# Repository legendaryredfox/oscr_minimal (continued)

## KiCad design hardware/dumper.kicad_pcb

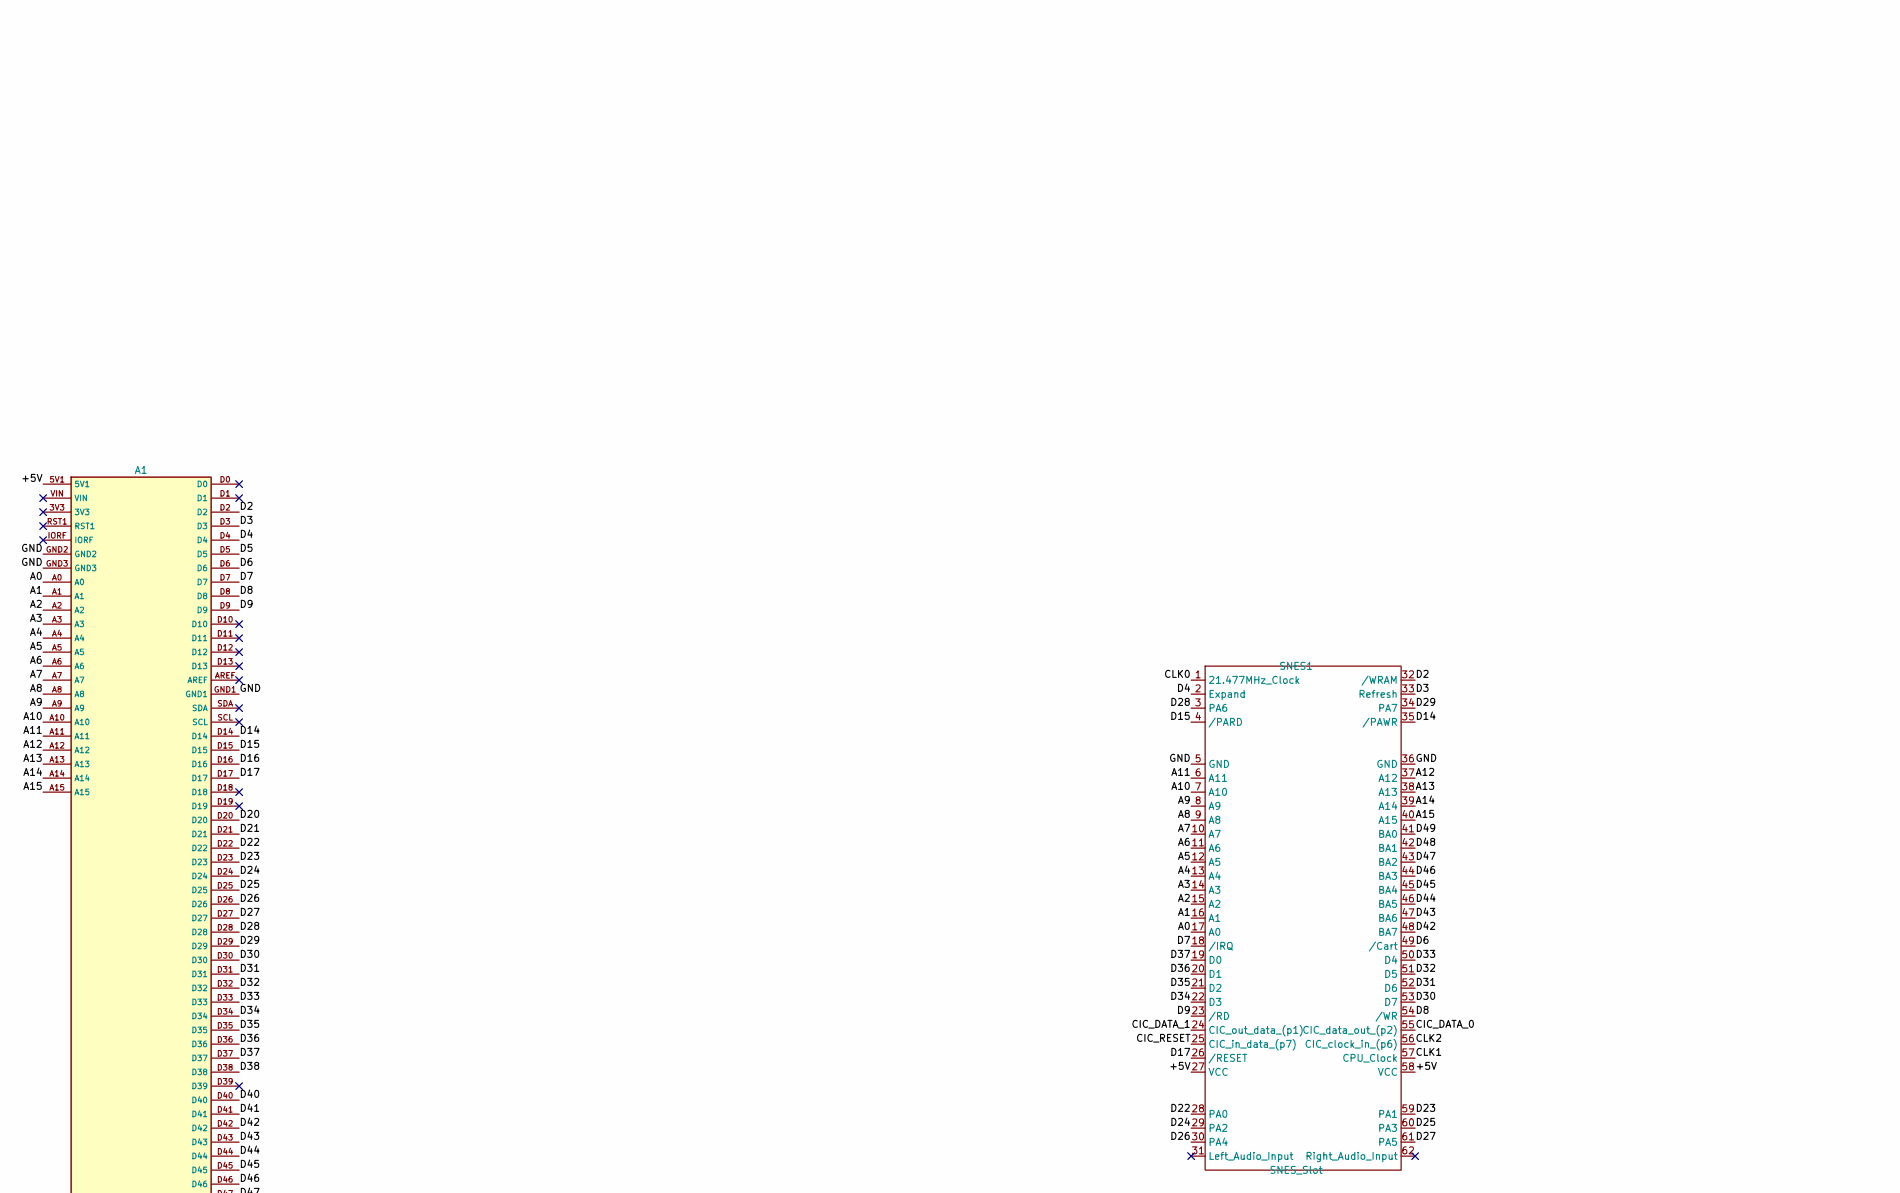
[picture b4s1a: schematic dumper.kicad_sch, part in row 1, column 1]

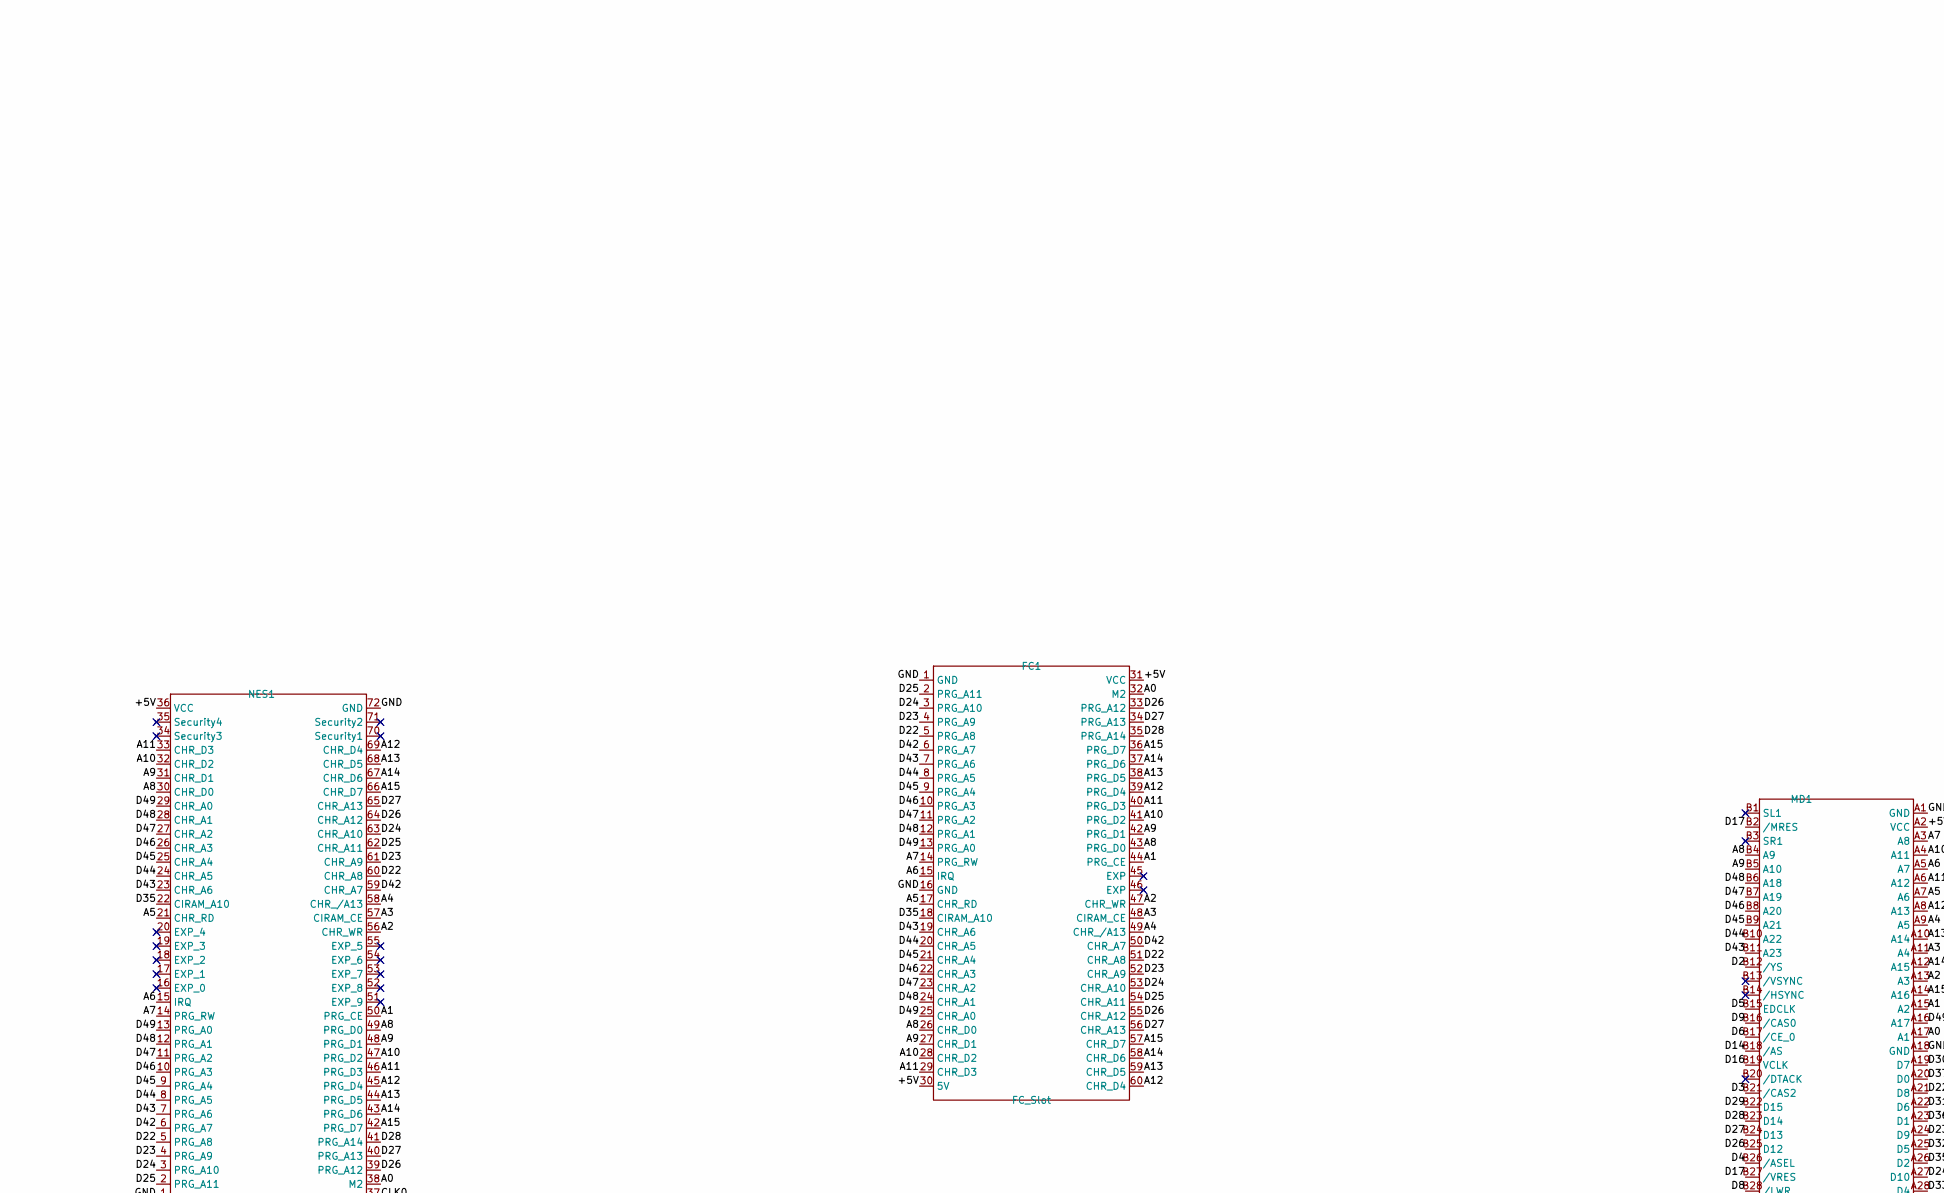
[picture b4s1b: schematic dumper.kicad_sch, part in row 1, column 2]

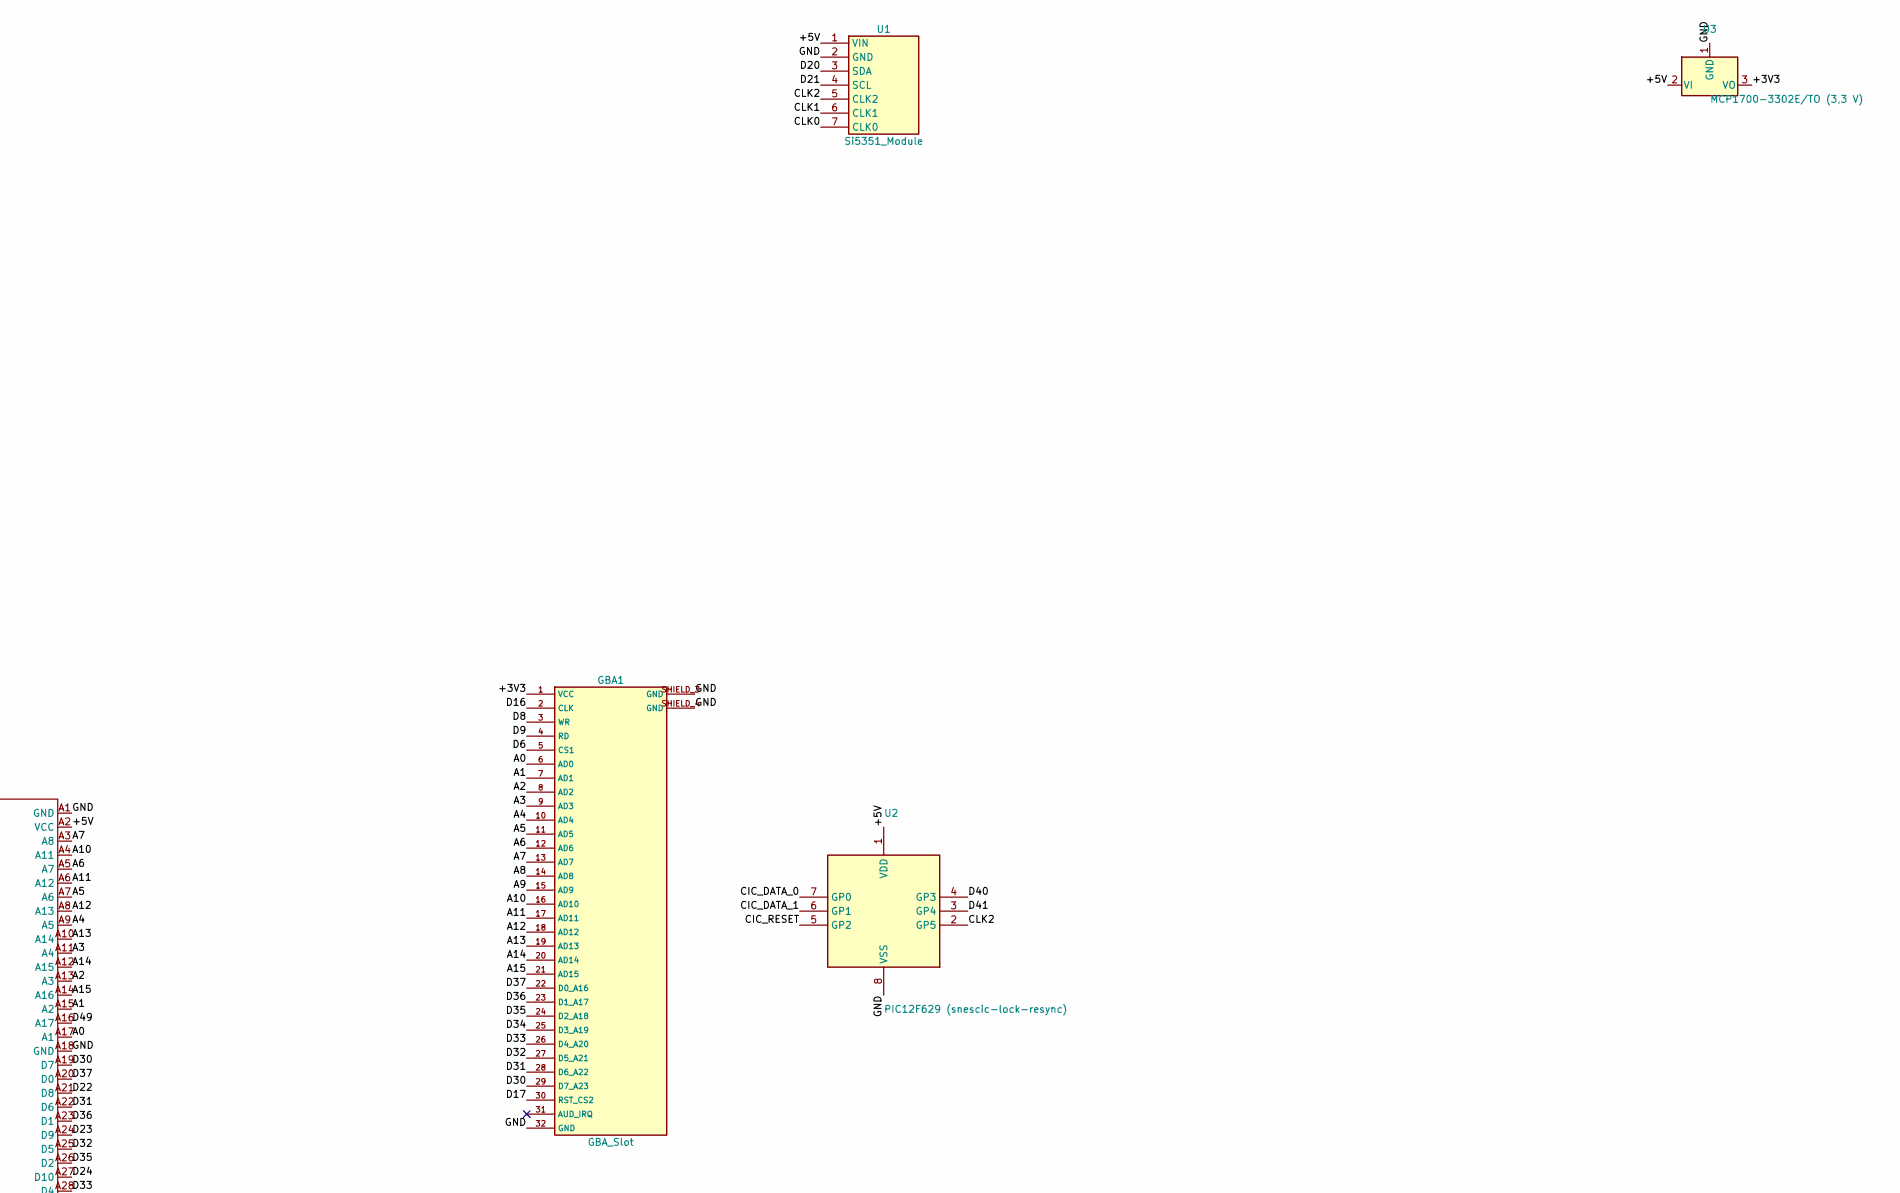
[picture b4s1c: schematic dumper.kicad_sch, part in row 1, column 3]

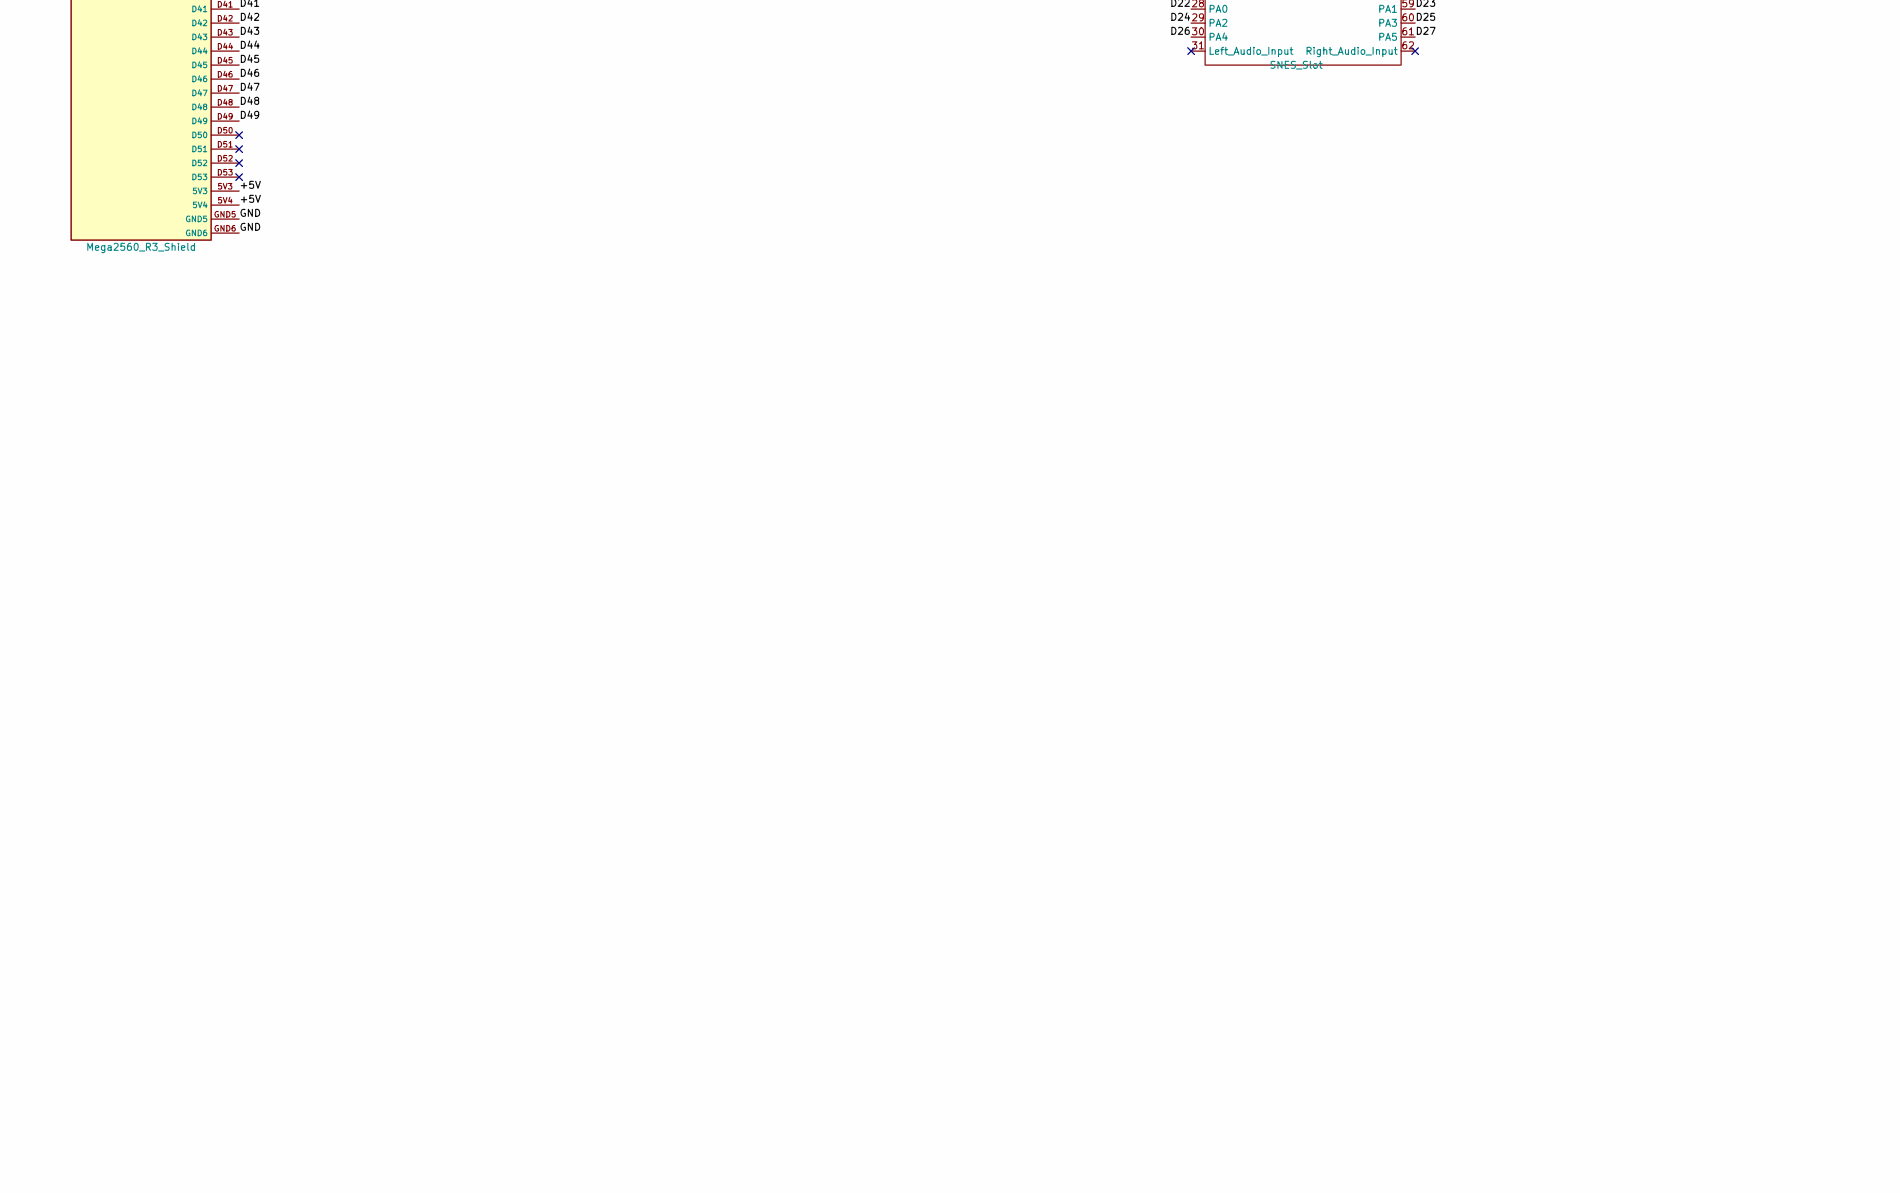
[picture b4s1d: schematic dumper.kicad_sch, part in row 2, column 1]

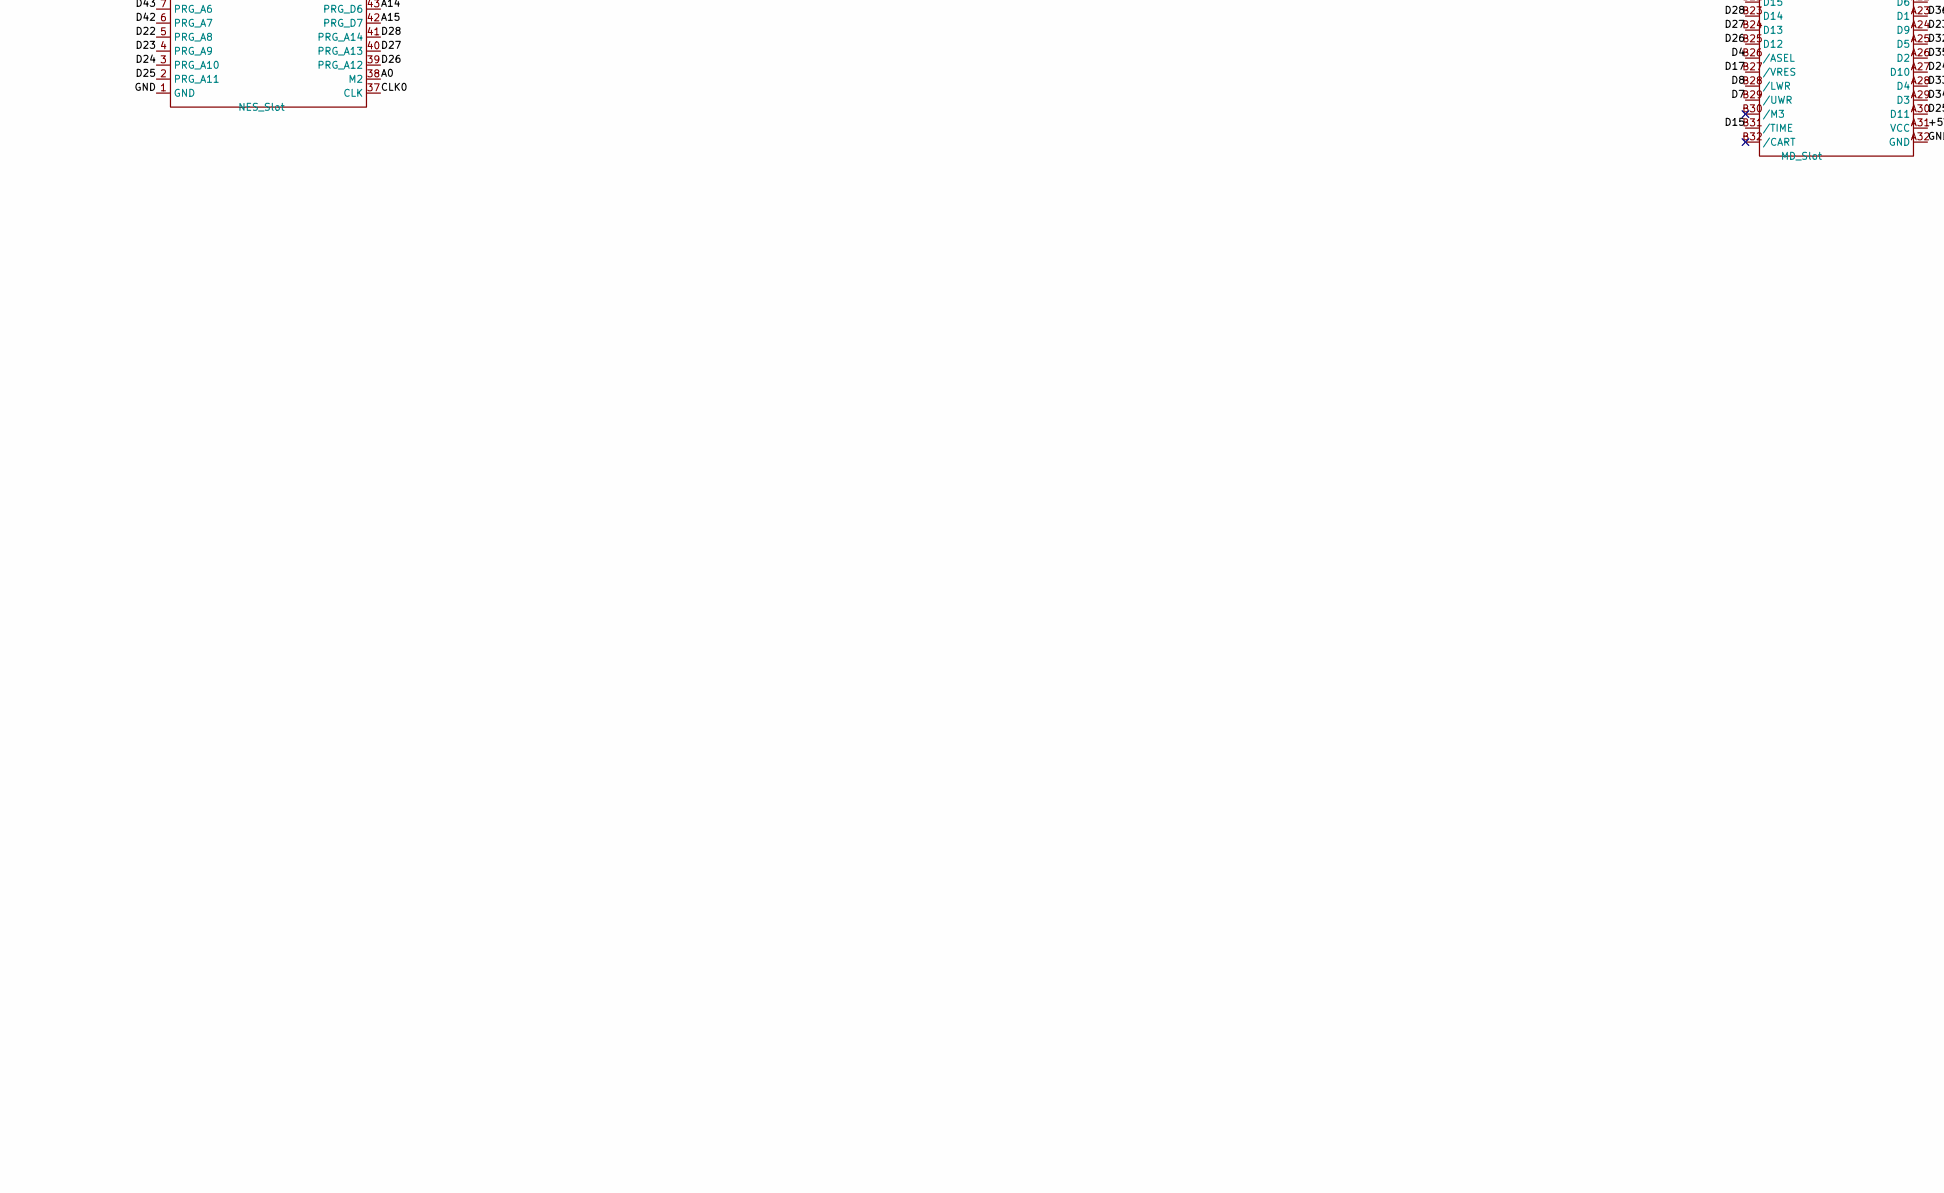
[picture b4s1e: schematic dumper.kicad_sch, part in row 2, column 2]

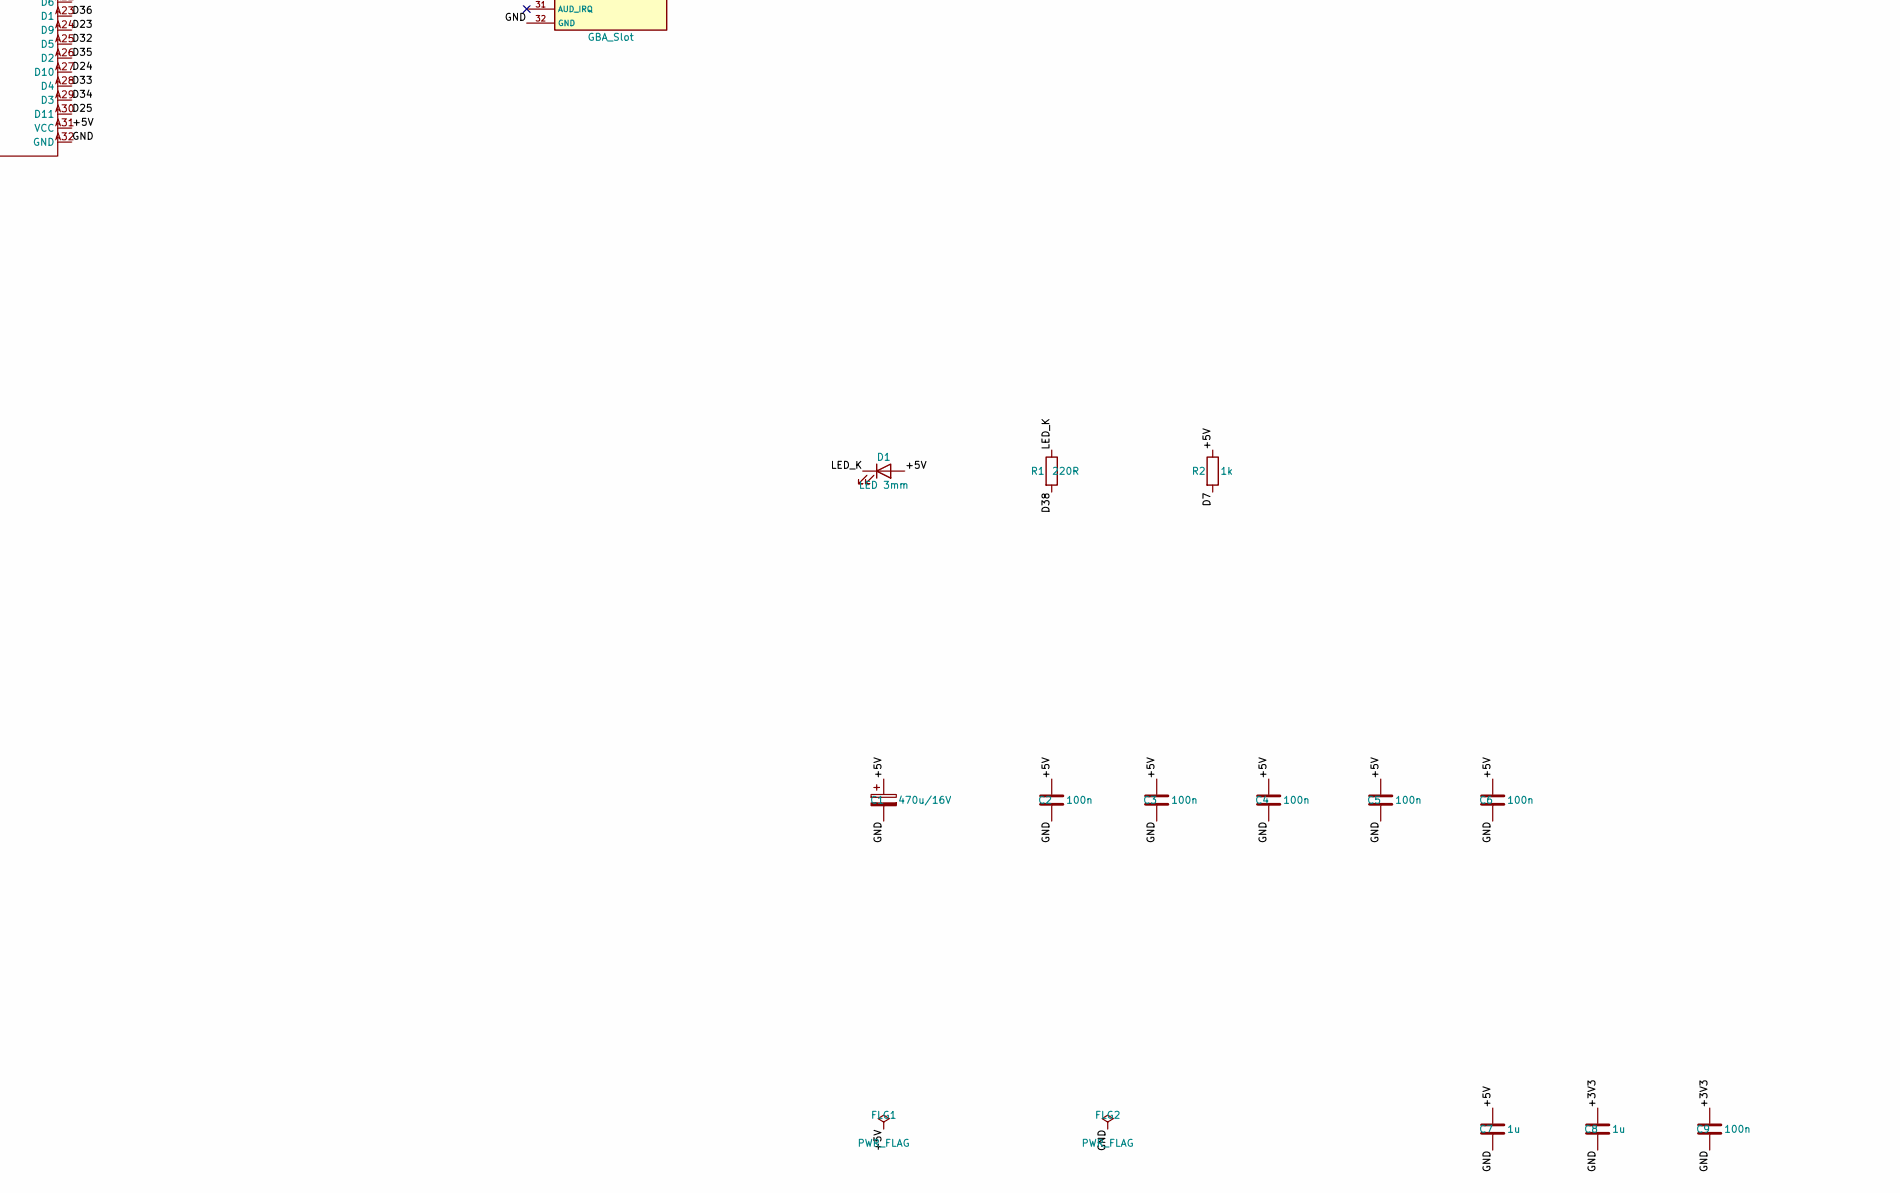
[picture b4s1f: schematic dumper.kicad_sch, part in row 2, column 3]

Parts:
A1: Mega2560_R3_Shield
C1: 470u/16V; CP_Radial_D8.0mm_P3.50mm
C2, C3, C4, C5, C6, C9: 100n; C_Disc_D5.0mm_W2.5mm_P5.00mm
C7, C8: 1u; C_Disc_D5.0mm_W2.5mm_P5.00mm
D1: LED 3mm; LED_D3.0mm
FC1: FC_Slot
FLG1, FLG2: PWR_FLAG
GBA1: GBA_Slot
MD1: MD_Slot
NES1: NES_Slot
R1: 220R; R_Axial_DIN0207_L6.3mm_D2.5mm_P10.16mm_Horizontal
R2: 1k; R_Axial_DIN0207_L6.3mm_D2.5mm_P10.16mm_Horizontal
SNES1: SNES_Slot
U1: Si5351_Module; PinSocket_1x07_P2.54mm_Vertical
U2: PIC12F629 (snescic-lock-resync); DIP-8_W7.62mm_Socket
U3: MCP1700-3302E/TO (3,3 V); TO-92_Inline

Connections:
/+3V3: C8.1, C9.1, GBA1.1 (VCC), U3.3 (VO)
/+5V: A1.5V1, A1.5V3, A1.5V4, C1.1, C2.1, C3.1, C4.1, C5.1, C6.1, C7.1, D1.2 (A), FC1.30 (5V), FC1.31 (VCC), FLG1.1, MD1.A2 (VCC), MD1.A31 (VCC), NES1.36 (VCC), R2.1, SNES1.27 (VCC), SNES1.58 (VCC), U1.1 (VIN), U2.1 (VDD), U3.2 (VI)
/A0: A1.A0, FC1.32 (M2), GBA1.6 (AD0), MD1.A17 (A1), NES1.38 (M2), SNES1.17 (A0)
/A1: A1.A1, FC1.44 (PRG_CE), GBA1.7 (AD1), MD1.A15 (A2), NES1.50 (PRG_CE), SNES1.16 (A1)
/A2: A1.A2, FC1.47 (CHR_WR), GBA1.8 (AD2), MD1.A13 (A3), NES1.56 (CHR_WR), SNES1.15 (A2)
/A3: A1.A3, FC1.48 (CIRAM_CE), GBA1.9 (AD3), MD1.A11 (A4), NES1.57 (CIRAM_CE), SNES1.14 (A3)
/A4: A1.A4, FC1.49 (CHR_/A13), GBA1.10 (AD4), MD1.A9 (A5), NES1.58 (CHR_/A13), SNES1.13 (A4)
/A5: A1.A5, FC1.17 (CHR_RD), GBA1.11 (AD5), MD1.A7 (A6), NES1.21 (CHR_RD), SNES1.12 (A5)
/A6: A1.A6, FC1.15 (IRQ), GBA1.12 (AD6), MD1.A5 (A7), NES1.15 (IRQ), SNES1.11 (A6)
/A7: A1.A7, FC1.14 (PRG_RW), GBA1.13 (AD7), MD1.A3 (A8), NES1.14 (PRG_RW), SNES1.10 (A7)
/A8: A1.A8, FC1.26 (CHR_D0), FC1.43 (PRG_D0), GBA1.14 (AD8), MD1.B4 (A9), NES1.30 (CHR_D0), NES1.49 (PRG_D0), SNES1.9 (A8)
/A9: A1.A9, FC1.27 (CHR_D1), FC1.42 (PRG_D1), GBA1.15 (AD9), MD1.B5 (A10), NES1.31 (CHR_D1), NES1.48 (PRG_D1), SNES1.8 (A9)
/A10: A1.A10, FC1.28 (CHR_D2), FC1.41 (PRG_D2), GBA1.16 (AD10), MD1.A4 (A11), NES1.32 (CHR_D2), NES1.47 (PRG_D2), SNES1.7 (A10)
/A11: A1.A11, FC1.29 (CHR_D3), FC1.40 (PRG_D3), GBA1.17 (AD11), MD1.A6 (A12), NES1.33 (CHR_D3), NES1.46 (PRG_D3), SNES1.6 (A11)
/A12: A1.A12, FC1.39 (PRG_D4), FC1.60 (CHR_D4), GBA1.18 (AD12), MD1.A8 (A13), NES1.45 (PRG_D4), NES1.69 (CHR_D4), SNES1.37 (A12)
/A13: A1.A13, FC1.38 (PRG_D5), FC1.59 (CHR_D5), GBA1.19 (AD13), MD1.A10 (A14), NES1.44 (PRG_D5), NES1.68 (CHR_D5), SNES1.38 (A13)
/A14: A1.A14, FC1.37 (PRG_D6), FC1.58 (CHR_D6), GBA1.20 (AD14), MD1.A12 (A15), NES1.43 (PRG_D6), NES1.67 (CHR_D6), SNES1.39 (A14)
/A15: A1.A15, FC1.36 (PRG_D7), FC1.57 (CHR_D7), GBA1.21 (AD15), MD1.A14 (A16), NES1.42 (PRG_D7), NES1.66 (CHR_D7), SNES1.40 (A15)
/CIC_DATA_0: SNES1.55 (CIC_data_out_(p2)), U2.7 (GP0)
/CIC_DATA_1: SNES1.24 (CIC_out_data_(p1)), U2.6 (GP1)
/CIC_RESET: SNES1.25 (CIC_in_data_(p7)), U2.5 (GP2)
/CLK0: NES1.37 (CLK), SNES1.1 (21.477MHz_Clock), U1.7 (CLK0)
/CLK1: SNES1.57 (CPU_Clock), U1.6 (CLK1)
/CLK2: SNES1.56 (CIC_clock_in_(p6)), U1.5 (CLK2), U2.2 (GP5)
/D2: A1.D2, MD1.B12 (/YS), SNES1.32 (/WRAM)
/D3: A1.D3, MD1.B21 (/CAS2), SNES1.33 (Refresh)
/D4: A1.D4, MD1.B26 (/ASEL), SNES1.2 (Expand)
/D5: A1.D5, MD1.B15 (EDCLK)
/D6: A1.D6, GBA1.5 (CS1), MD1.B17 (/CE_0), SNES1.49 (/Cart)
/D7: A1.D7, MD1.B29 (/UWR), R2.2, SNES1.18 (/IRQ)
/D8: A1.D8, GBA1.3 (WR), MD1.B28 (/LWR), SNES1.54 (/WR)
/D9: A1.D9, GBA1.4 (RD), MD1.B16 (/CAS0), SNES1.23 (/RD)
/D14: A1.D14, MD1.B18 (/AS), SNES1.35 (/PAWR)
/D15: A1.D15, MD1.B31 (/TIME), SNES1.4 (/PARD)
/D16: A1.D16, GBA1.2 (CLK), MD1.B19 (VCLK)
/D17: A1.D17, GBA1.30 (RST_CS2), MD1.B2 (/MRES), MD1.B27 (/VRES), SNES1.26 (/RESET)
/D20: A1.D20, U1.3 (SDA)
/D21: A1.D21, U1.4 (SCL)
/D22: A1.D22, FC1.5 (PRG_A8), FC1.51 (CHR_A8), MD1.A21 (D8), NES1.5 (PRG_A8), NES1.60 (CHR_A8), SNES1.28 (PA0)
/D23: A1.D23, FC1.4 (PRG_A9), FC1.52 (CHR_A9), MD1.A24 (D9), NES1.4 (PRG_A9), NES1.61 (CHR_A9), SNES1.59 (PA1)
/D24: A1.D24, FC1.3 (PRG_A10), FC1.53 (CHR_A10), MD1.A27 (D10), NES1.3 (PRG_A10), NES1.63 (CHR_A10), SNES1.29 (PA2)
/D25: A1.D25, FC1.2 (PRG_A11), FC1.54 (CHR_A11), MD1.A30 (D11), NES1.2 (PRG_A11), NES1.62 (CHR_A11), SNES1.60 (PA3)
/D26: A1.D26, FC1.33 (PRG_A12), FC1.55 (CHR_A12), MD1.B25 (D12), NES1.39 (PRG_A12), NES1.64 (CHR_A12), SNES1.30 (PA4)
/D27: A1.D27, FC1.34 (PRG_A13), FC1.56 (CHR_A13), MD1.B24 (D13), NES1.40 (PRG_A13), NES1.65 (CHR_A13), SNES1.61 (PA5)
/D28: A1.D28, FC1.35 (PRG_A14), MD1.B23 (D14), NES1.41 (PRG_A14), SNES1.3 (PA6)
/D29: A1.D29, MD1.B22 (D15), SNES1.34 (PA7)
/D30: A1.D30, GBA1.29 (D7_A23), MD1.A19 (D7), SNES1.53 (D7)
/D31: A1.D31, GBA1.28 (D6_A22), MD1.A22 (D6), SNES1.52 (D6)
/D32: A1.D32, GBA1.27 (D5_A21), MD1.A25 (D5), SNES1.51 (D5)
/D33: A1.D33, GBA1.26 (D4_A20), MD1.A28 (D4), SNES1.50 (D4)
/D34: A1.D34, GBA1.25 (D3_A19), MD1.A29 (D3), SNES1.22 (D3)
/D35: A1.D35, FC1.18 (CIRAM_A10), GBA1.24 (D2_A18), MD1.A26 (D2), NES1.22 (CIRAM_A10), SNES1.21 (D2)
/D36: A1.D36, GBA1.23 (D1_A17), MD1.A23 (D1), SNES1.20 (D1)
/D37: A1.D37, GBA1.22 (D0_A16), MD1.A20 (D0), SNES1.19 (D0)
/D38: A1.D38, R1.2
/D40: A1.D40, U2.4 (GP3)
/D41: A1.D41, U2.3 (GP4)
/D42: A1.D42, FC1.6 (PRG_A7), FC1.50 (CHR_A7), NES1.6 (PRG_A7), NES1.59 (CHR_A7), SNES1.48 (BA7)
/D43: A1.D43, FC1.7 (PRG_A6), FC1.19 (CHR_A6), MD1.B11 (A23), NES1.7 (PRG_A6), NES1.23 (CHR_A6), SNES1.47 (BA6)
/D44: A1.D44, FC1.8 (PRG_A5), FC1.20 (CHR_A5), MD1.B10 (A22), NES1.8 (PRG_A5), NES1.24 (CHR_A5), SNES1.46 (BA5)
/D45: A1.D45, FC1.9 (PRG_A4), FC1.21 (CHR_A4), MD1.B9 (A21), NES1.9 (PRG_A4), NES1.25 (CHR_A4), SNES1.45 (BA4)
/D46: A1.D46, FC1.10 (PRG_A3), FC1.22 (CHR_A3), MD1.B8 (A20), NES1.10 (PRG_A3), NES1.26 (CHR_A3), SNES1.44 (BA3)
/D47: A1.D47, FC1.11 (PRG_A2), FC1.23 (CHR_A2), MD1.B7 (A19), NES1.11 (PRG_A2), NES1.27 (CHR_A2), SNES1.43 (BA2)
/D48: A1.D48, FC1.12 (PRG_A1), FC1.24 (CHR_A1), MD1.B6 (A18), NES1.12 (PRG_A1), NES1.28 (CHR_A1), SNES1.42 (BA1)
/D49: A1.D49, FC1.13 (PRG_A0), FC1.25 (CHR_A0), MD1.A16 (A17), NES1.13 (PRG_A0), NES1.29 (CHR_A0), SNES1.41 (BA0)
/GND: A1.GND1, A1.GND2, A1.GND3, A1.GND5, A1.GND6, C1.2, C2.2, C3.2, C4.2, C5.2, C6.2, C7.2, C8.2, C9.2, FC1.1 (GND), FC1.16 (GND), FLG2.1, GBA1.32 (GND), GBA1.SHIELD_3 (GND), GBA1.SHIELD_4 (GND), MD1.A1 (GND), MD1.A18 (GND), MD1.A32 (GND), NES1.1 (GND), NES1.72 (GND), SNES1.5 (GND), SNES1.36 (GND), U1.2 (GND), U2.8 (VSS), U3.1 (GND)
/LED_K: D1.1 (K), R1.1

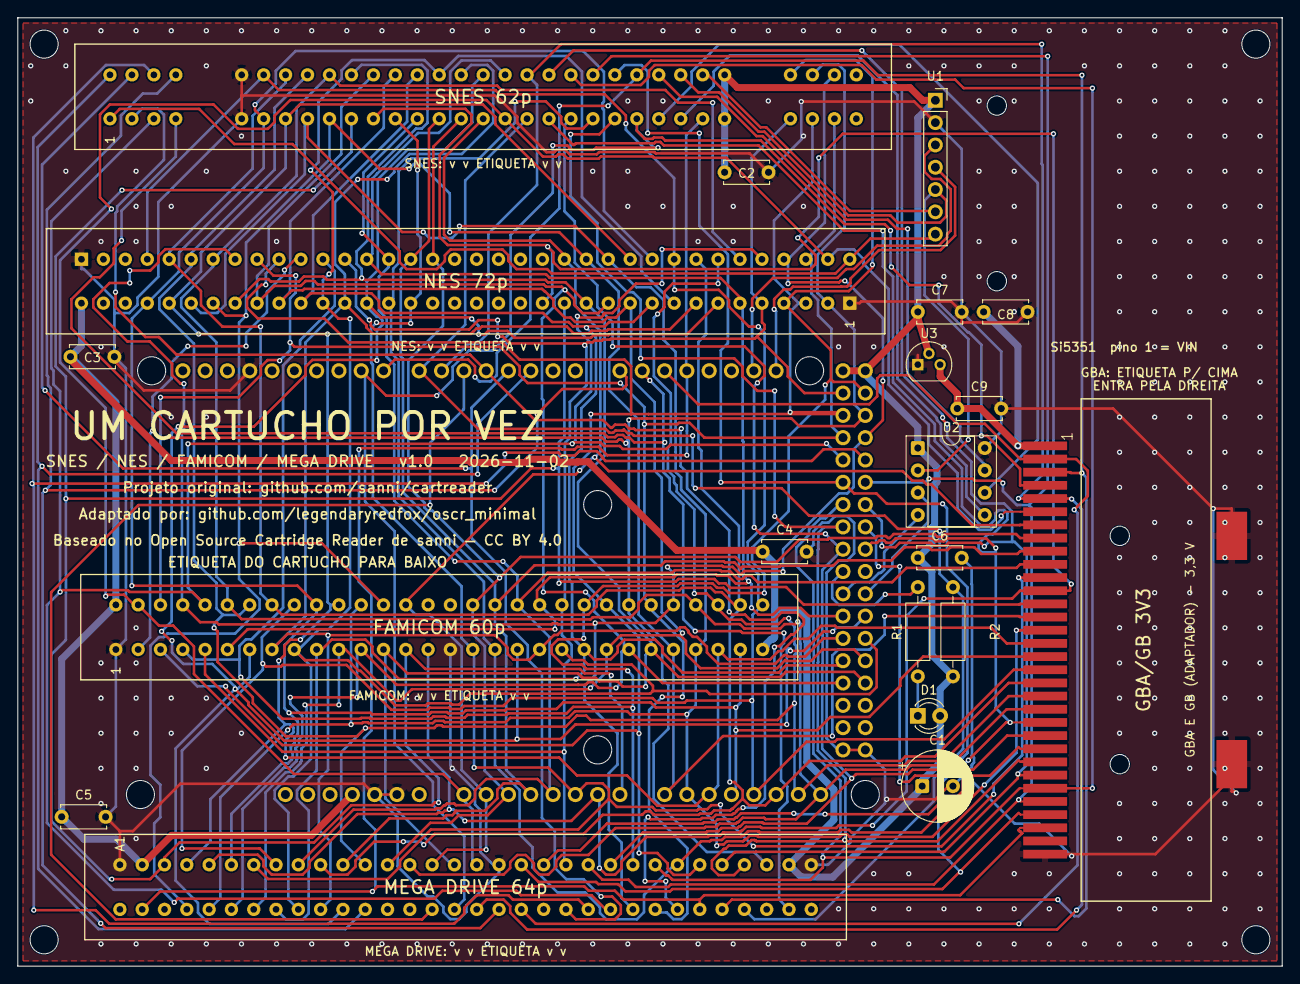
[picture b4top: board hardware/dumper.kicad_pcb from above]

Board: 2 copper layers, 144.0 x 108.0 mm, 27 parts (0 on the bottom side), 67 nets.

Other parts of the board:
MH1, MH2, MH3, MH4: MountingHole_3.2mm; MountingHole_3.2mm_M3
MH5, MH6: MountingHole_2.2mm_M2
